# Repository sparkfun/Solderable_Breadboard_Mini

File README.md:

Solder-able Breadboard
=======================

[
*Solderable Breadboard-Mini(PRT-12702)*](https://www.sparkfun.com/products/12702)

This is a bare pcb that is the same size as a mini (35 x 50 mm) breadboard.  It only has the DIP pattern traces, and no power rails.

Repository Contents
-------------------
* **/Hardware** - All Eagle design files (.brd, .sch)

License Information
-------------------
The hardware is released under [Creative Commons Share-alike 3.0](http://creativecommons.org/licenses/by-sa/3.0/).

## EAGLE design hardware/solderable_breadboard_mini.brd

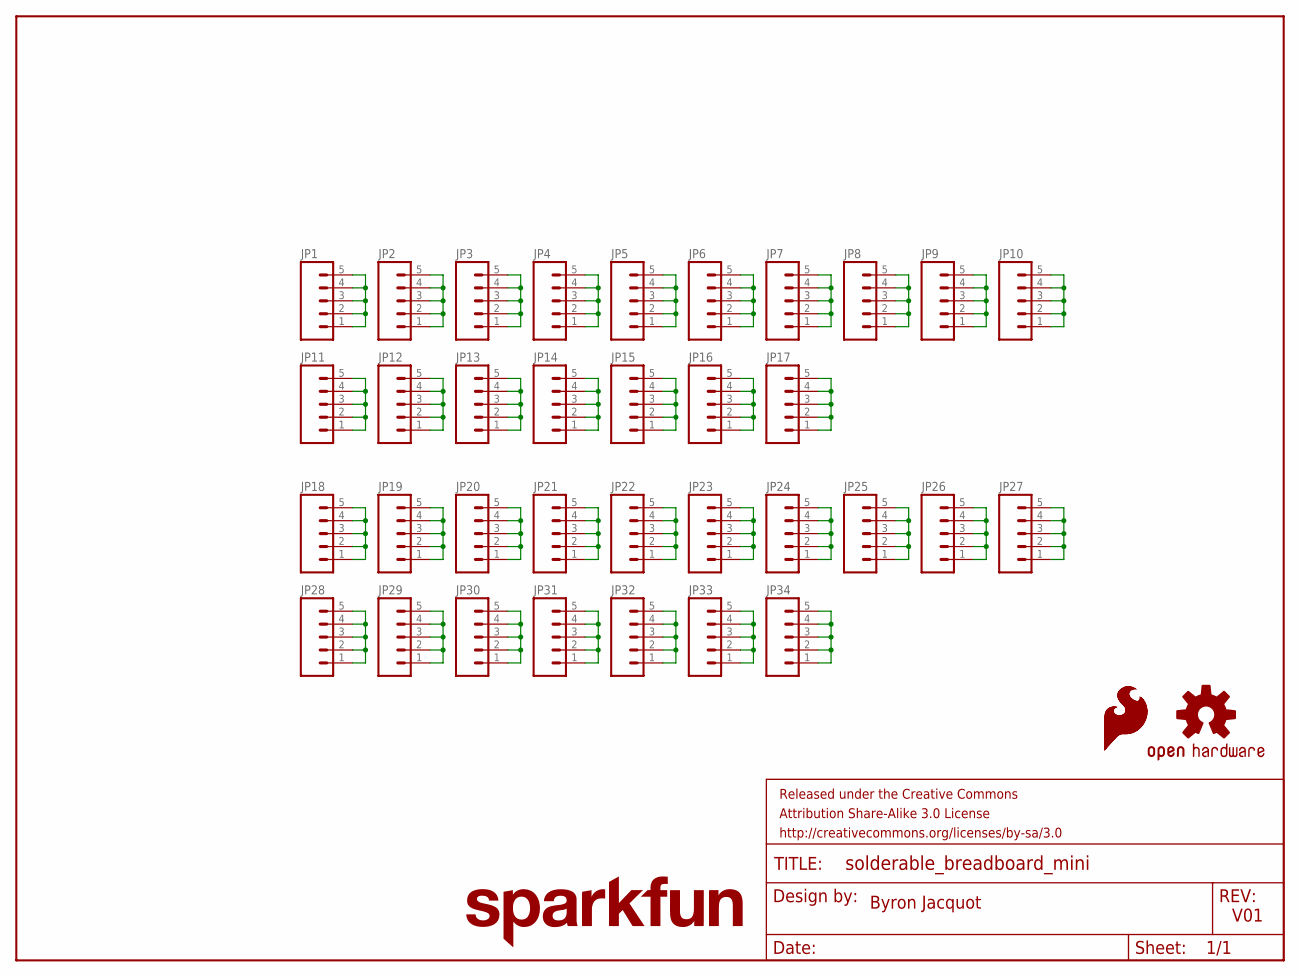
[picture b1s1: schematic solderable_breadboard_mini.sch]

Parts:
FRAME1: FRAME-LETTER; CREATIVE_COMMONS
JP1, JP2, JP3, JP4, JP5, JP6, JP7, JP8, JP9, JP10, JP11, JP12, JP13, JP14, JP15, JP16, JP17, JP18, JP19, JP20, JP21, JP22, JP23, JP24, JP25, JP26, JP27, JP28, JP29, JP30, JP31, JP32, JP33, JP34: 1X05_NO_SILK
LOGO1: SFE_LOGO_NAME.1_INCH; SFE_LOGO_NAME_.1
LOGO2: OSHW-LOGOM; OSHW-LOGO-M
LOGO3, LOGO4: SFE_LOGO_FLAME.1_INCH; SFE_LOGO_FLAME_.1

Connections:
unnamed: JP1.1, JP1.2, JP1.3, JP1.4, JP1.5
unnamed: JP2.1, JP2.2, JP2.3, JP2.4, JP2.5
unnamed: JP3.1, JP3.2, JP3.3, JP3.4, JP3.5
unnamed: JP4.1, JP4.2, JP4.3, JP4.4, JP4.5
unnamed: JP5.1, JP5.2, JP5.3, JP5.4, JP5.5
unnamed: JP6.1, JP6.2, JP6.3, JP6.4, JP6.5
unnamed: JP7.1, JP7.2, JP7.3, JP7.4, JP7.5
unnamed: JP8.1, JP8.2, JP8.3, JP8.4, JP8.5
unnamed: JP9.1, JP9.2, JP9.3, JP9.4, JP9.5
unnamed: JP10.1, JP10.2, JP10.3, JP10.4, JP10.5
unnamed: JP11.1, JP11.2, JP11.3, JP11.4, JP11.5
unnamed: JP12.1, JP12.2, JP12.3, JP12.4, JP12.5
unnamed: JP13.1, JP13.2, JP13.3, JP13.4, JP13.5
unnamed: JP14.1, JP14.2, JP14.3, JP14.4, JP14.5
unnamed: JP15.1, JP15.2, JP15.3, JP15.4, JP15.5
unnamed: JP16.1, JP16.2, JP16.3, JP16.4, JP16.5
unnamed: JP17.1, JP17.2, JP17.3, JP17.4, JP17.5
unnamed: JP18.1, JP18.2, JP18.3, JP18.4, JP18.5
unnamed: JP19.1, JP19.2, JP19.3, JP19.4, JP19.5
unnamed: JP20.1, JP20.2, JP20.3, JP20.4, JP20.5
unnamed: JP21.1, JP21.2, JP21.3, JP21.4, JP21.5
unnamed: JP22.1, JP22.2, JP22.3, JP22.4, JP22.5
unnamed: JP23.1, JP23.2, JP23.3, JP23.4, JP23.5
unnamed: JP24.1, JP24.2, JP24.3, JP24.4, JP24.5
unnamed: JP25.1, JP25.2, JP25.3, JP25.4, JP25.5
unnamed: JP26.1, JP26.2, JP26.3, JP26.4, JP26.5
unnamed: JP27.1, JP27.2, JP27.3, JP27.4, JP27.5
unnamed: JP28.1, JP28.2, JP28.3, JP28.4, JP28.5
unnamed: JP29.1, JP29.2, JP29.3, JP29.4, JP29.5
unnamed: JP30.1, JP30.2, JP30.3, JP30.4, JP30.5
unnamed: JP31.1, JP31.2, JP31.3, JP31.4, JP31.5
unnamed: JP32.1, JP32.2, JP32.3, JP32.4, JP32.5
unnamed: JP33.1, JP33.2, JP33.3, JP33.4, JP33.5
unnamed: JP34.1, JP34.2, JP34.3, JP34.4, JP34.5

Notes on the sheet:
Byron Jacquot
V01

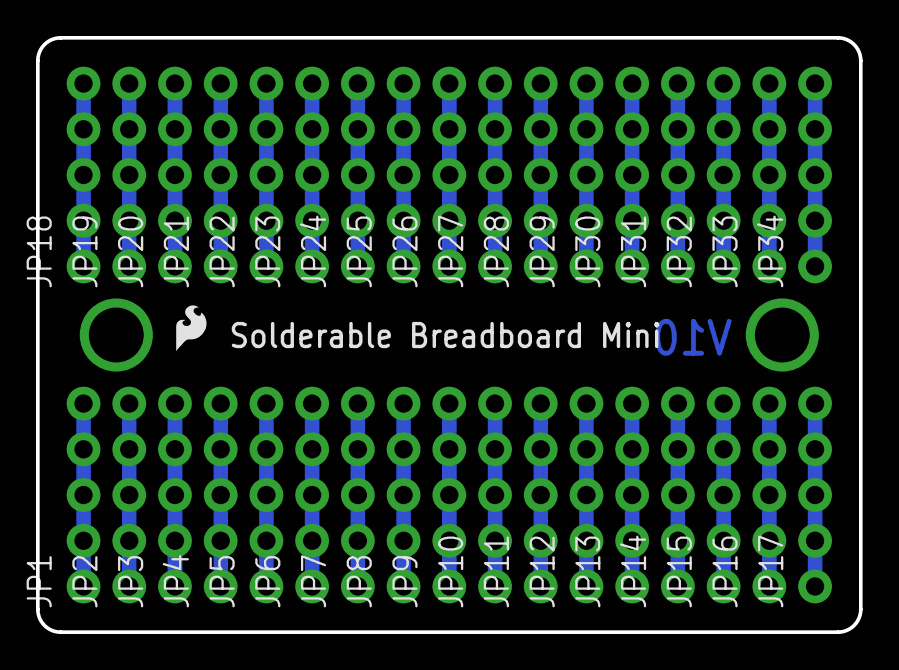
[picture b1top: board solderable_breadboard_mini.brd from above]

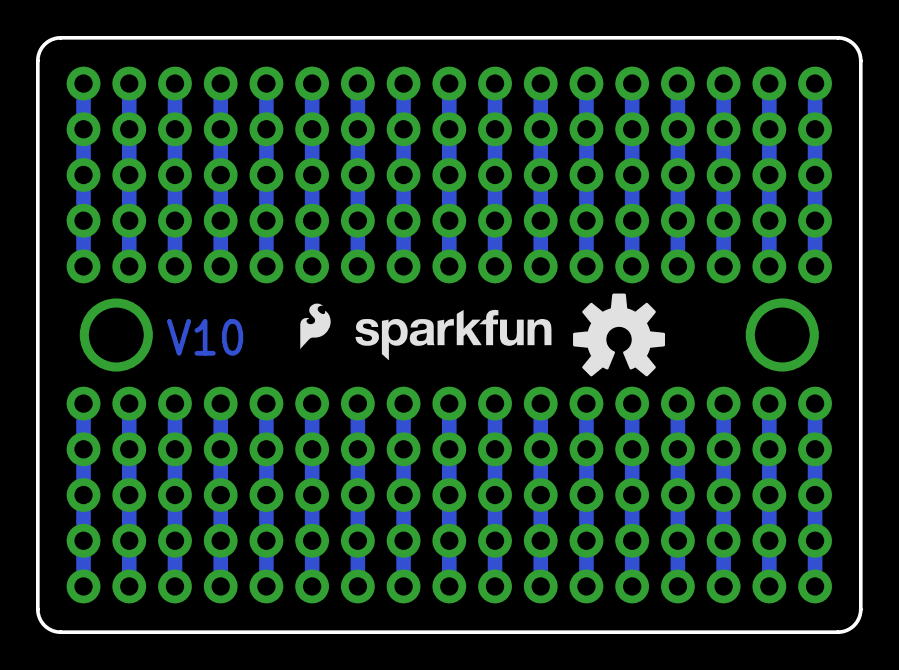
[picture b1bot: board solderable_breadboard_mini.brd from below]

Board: 2 copper layers, 45.7 x 33.0 mm, 39 parts (3 on the bottom side), 34 nets.

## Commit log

2014-01-03 First batch of files
2014-01-06 Adding some flame logos to the board.
2014-01-21 Ready for reds
    Outline a tiny bit smaller.
    Silkscreen elements more balanced.
2014-01-29 Updates after group review.
    Mounting holes can now clear a 4-40, but a 2-56 head won't fall through.
2014-03-13 Adding product link to readme

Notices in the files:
parts and their libraries:
SparkFun-Aesthetics: Licensing: CC v3.0 Share-Alike You are welcome to use this library for commercial purposes.
SparkFun-Aesthetics: Released under the Creative Commons Attribution Share-Alike 3.0 License
SparkFun-Aesthetics: Released under the Creative Commons
